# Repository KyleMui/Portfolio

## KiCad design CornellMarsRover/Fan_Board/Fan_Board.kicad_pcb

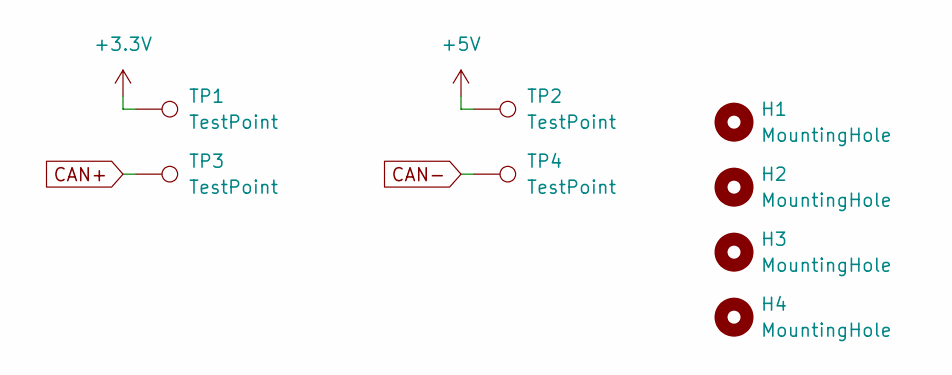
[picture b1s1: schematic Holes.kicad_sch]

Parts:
H1, H2, H3, H4: MountingHole; MountingHole_3.2mm_M3
TP1, TP2, TP3, TP4: TestPoint; TestPoint_Pad_D1.0mm

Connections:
+3.3V: TP1.1; also elsewhere on the board
+5V: TP2.1; also elsewhere on the board
CAN+: TP3.1; also elsewhere on the board
CAN-: TP4.1; also elsewhere on the board

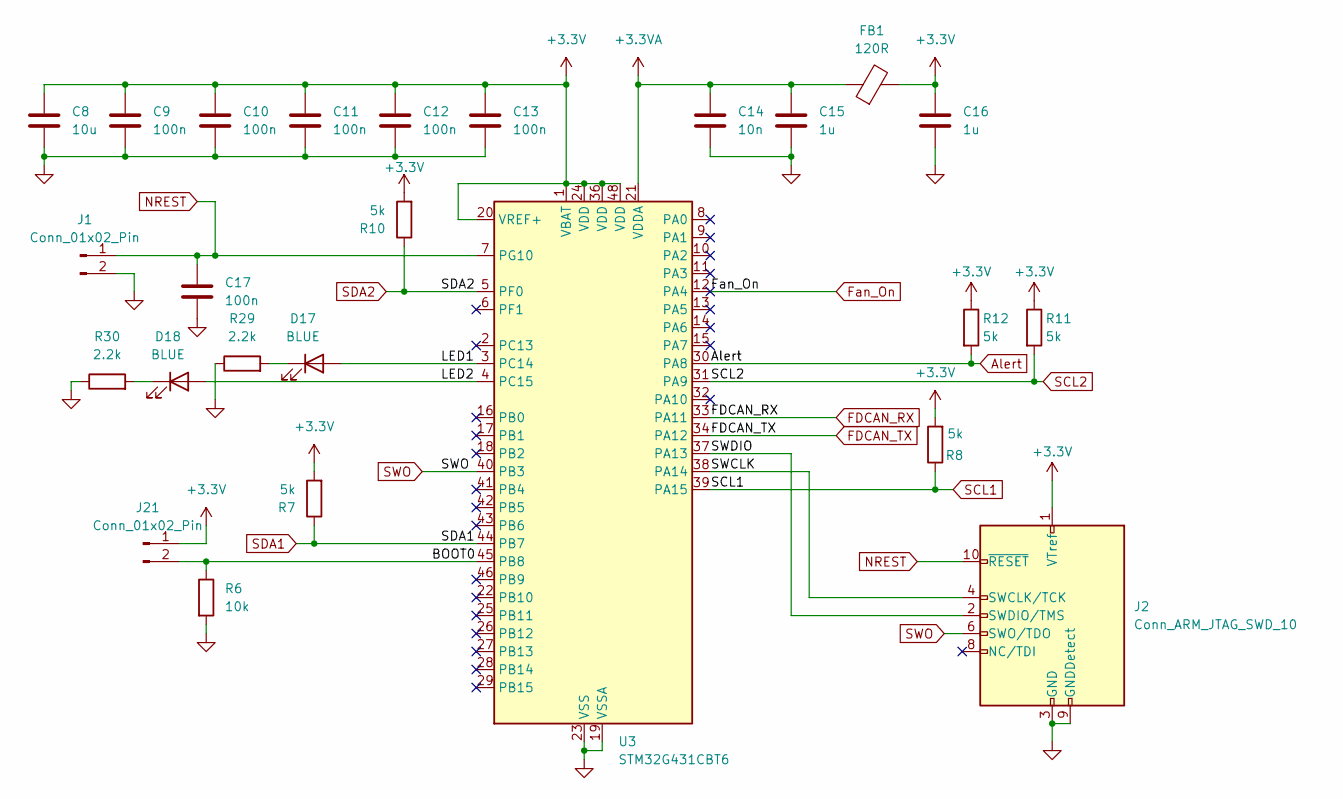
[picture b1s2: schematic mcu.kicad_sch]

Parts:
C8: 10u; C_0603_1608Metric
C9, C10, C11, C12, C13, C17: 100n; C_0402_1005Metric
C14: 10n; C_0402_1005Metric
C15, C16: 1u; C_0402_1005Metric
D17, D18: BLUE; LED_0603_1608Metric
FB1: 120R; L_0603_1608Metric
J1: Conn_01x02_Pin; PinHeader_1x02_P2.54mm_Horizontal
J2: Conn_ARM_JTAG_SWD_10; PinHeader_2x05_P1.27mm_Vertical
J21: Conn_01x02_Pin; PinHeader_1x02_P2.54mm_Vertical
R6: 10k; R_0402_1005Metric
R7, R8, R10, R11, R12: 5k; R_0402_1005Metric
R29, R30: 2.2k; R_0402_1005Metric
U3: STM32G431CBT6; LQFP-48_7x7mm_P0.5mm

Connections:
+3.3V: C8.1, C9.1, C10.1, C11.1, C12.1, C13.1, C16.1, FB1.2, J2.1 (VTref), J21.1, R7.2, R8.2, R10.2, R11.1, R12.1, U3.1 (VBAT), U3.20 (VREF+), U3.24 (VDD), U3.36 (VDD), U3.48 (VDD); also elsewhere on the board
+3.3VA: C14.1, C15.1, FB1.1, U3.21 (VDDA)
/MCU/BOOT0: J21.2, R6.1, U3.45 (PB8)
/MCU/LED1: D17.2 (A), U3.3 (PC14)
/MCU/LED2: D18.2 (A), U3.4 (PC15)
/MCU/SWCLK: J2.4 (SWCLK/TCK), U3.38 (PA14)
/MCU/SWDIO: J2.2 (SWDIO/TMS), U3.37 (PA13)
Alert: R12.2, U3.30 (PA8); also elsewhere on the board
FDCAN_RX: U3.33 (PA11); also elsewhere on the board
FDCAN_TX: U3.34 (PA12); also elsewhere on the board
Fan_On: U3.12 (PA4); also elsewhere on the board
GND: C8.2, C9.2, C10.2, C11.2, C12.2, C13.2, C14.2, C15.2, C16.2, C17.2, J1.2, J2.3 (GND), J2.5 (GND), J2.9 (GNDDetect), R6.2, R29.1, R30.1, U3.19 (VSSA), U3.23 (VSS), U3.35 (VSS), U3.47 (VSS); also elsewhere on the board
NREST: C17.1, J1.1, J2.10 (~RESET), U3.7 (PG10)
unnamed: D17.1 (K), R29.2
unnamed: D18.1 (K), R30.2
SCL1: R8.1, U3.39 (PA15); also elsewhere on the board
SCL2: R11.2, U3.31 (PA9); also elsewhere on the board
SDA1: R7.1, U3.44 (PB7); also elsewhere on the board
SDA2: R10.1, U3.5 (PF0); also elsewhere on the board
SWO: J2.6 (SWO/TDO), U3.40 (PB3)

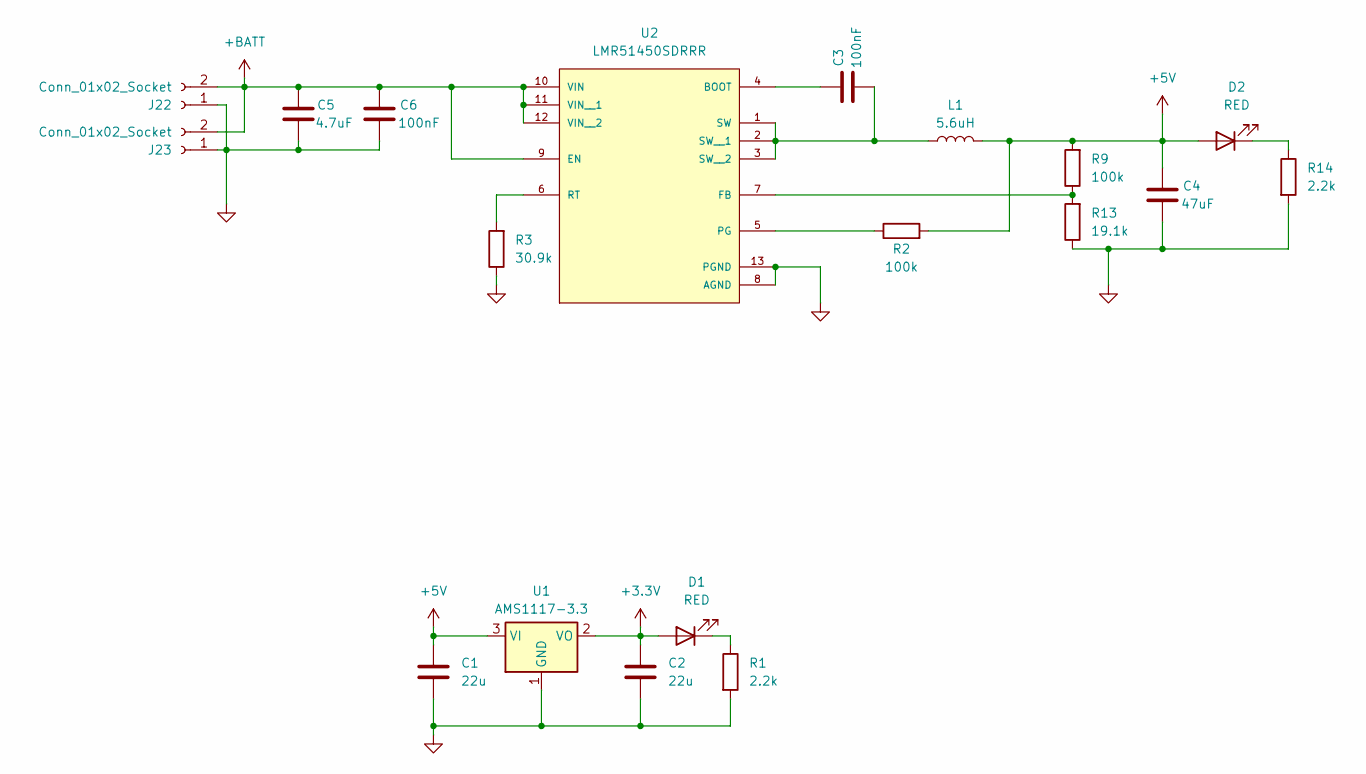
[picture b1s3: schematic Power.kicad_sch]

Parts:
C1, C2: 22u; C_0805_2012Metric
C3, C6: 100nF; C_0402_1005Metric
C4: 47uF; C_1210_3225Metric
C5: 4.7uF; C_1206_3216Metric
D1, D2: RED; LED_0603_1608Metric
J22, J23: Conn_01x02_Socket; AMASS_XT30PW-M_1x02_P2.50mm_Horizontal
L1: 5.6uH; L_Vishay_IHLP-4040
R1, R14: 2.2k; R_0402_1005Metric
R2, R9: 100k; R_0603_1608Metric
R3: 30.9k; R_0603_1608Metric
R13: 19.1k; R_0603_1608Metric
U1: AMS1117-3.3; SOT-223-3_TabPin2
U2: LMR51450SDRRR; CONV_LMR51450SDRRR; PARTREV December 2022

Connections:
+3.3V: C2.1, D1.2 (A), U1.2 (VO); also elsewhere on the board
+5V: C1.1, C4.1, D2.2 (A), L1.2, R2.2, R9.2, U1.3 (VI); also elsewhere on the board
+BATT: C5.1, C6.1, J22.2, J23.2, U2.9 (EN), U2.10 (VIN), U2.11 (VIN__1), U2.12 (VIN__2)
GND: C1.2, C2.2, C4.2, C5.2, C6.2, J22.1, J23.1, R1.2, R3.1, R13.1, R14.2, U1.1 (GND), U2.8 (AGND), U2.13 (PGND); also elsewhere on the board
unnamed: D1.1 (K), R1.1
unnamed: D2.1 (K), R14.1
unnamed: C3.1, U2.4 (BOOT)
unnamed: R9.1, R13.2, U2.7 (FB)
unnamed: R2.1, U2.5 (PG)
unnamed: R3.2, U2.6 (RT)
unnamed: C3.2, L1.1, U2.1 (SW), U2.2 (SW__1), U2.3 (SW__2)

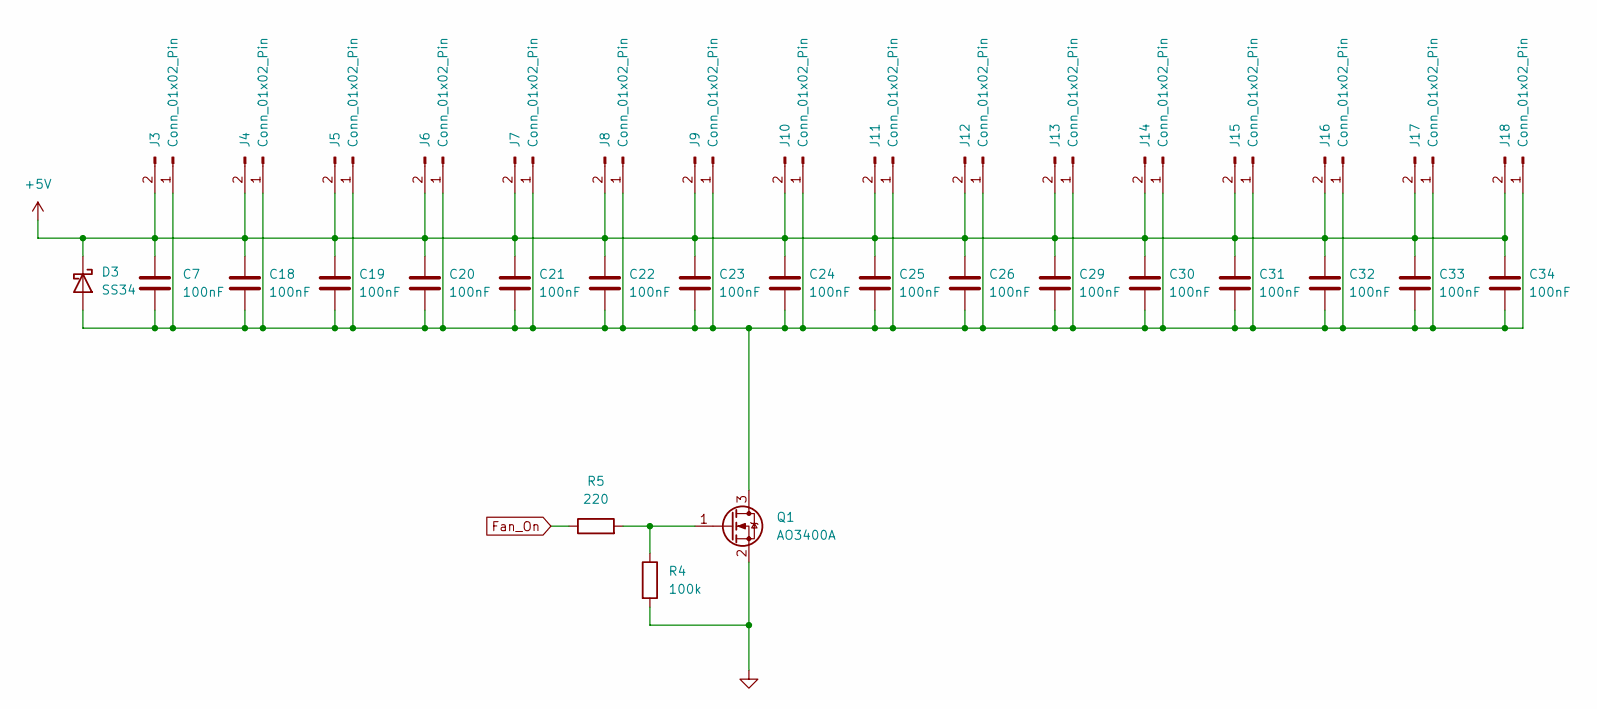
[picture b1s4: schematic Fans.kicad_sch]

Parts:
C7, C18, C19, C20, C21, C22, C23, C24, C25, C26, C29, C30, C31, C32, C33, C34: 100nF; C_0402_1005Metric
D3: SS34; D_SMA
J3, J4, J5, J6, J7, J8, J9, J10, J11, J12, J13, J14, J15, J16, J17, J18: Conn_01x02_Pin; JST_S2B-PH-SM4-TB
Q1: AO3400A; SOT-23
R4: 100k; R_0603_1608Metric
R5: 220; R_0603_1608Metric

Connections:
+5V: C7.1, C18.1, C19.1, C20.1, C21.1, C22.1, C23.1, C24.1, C25.1, C26.1, C29.1, C30.1, C31.1, C32.1, C33.1, C34.1, D3.1 (K), J3.2, J4.2, J5.2, J6.2, J7.2, J8.2, J9.2, J10.2, J11.2, J12.2, J13.2, J14.2, J15.2, J16.2, J17.2, J18.2; also elsewhere on the board
Fan_On: R5.1; also elsewhere on the board
GND: Q1.2 (S), R4.2; also elsewhere on the board
unnamed: C7.2, C18.2, C19.2, C20.2, C21.2, C22.2, C23.2, C24.2, C25.2, C26.2, C29.2, C30.2, C31.2, C32.2, C33.2, C34.2, D3.2 (A), J3.1, J4.1, J5.1, J6.1, J7.1, J8.1, J9.1, J10.1, J11.1, J12.1, J13.1, J14.1, J15.1, J16.1, J17.1, J18.1, Q1.3 (D)
unnamed: Q1.1 (G), R4.1, R5.2

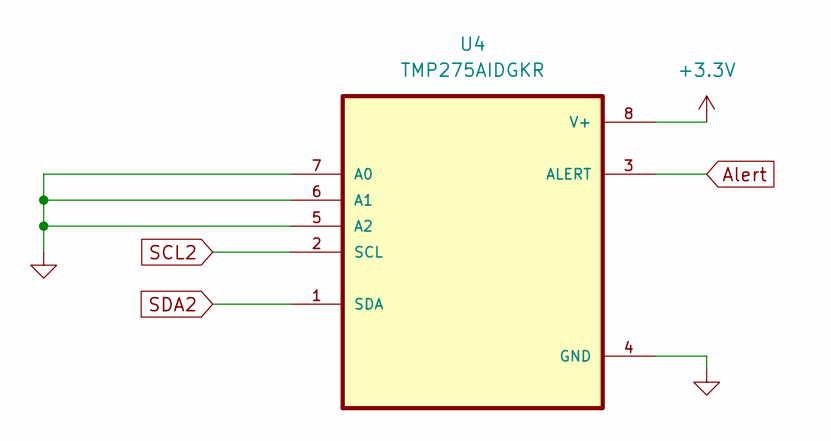
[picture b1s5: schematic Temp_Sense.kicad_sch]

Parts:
U4: TMP275AIDGKR; SOP65P490X110-8N

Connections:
+3.3V: U4.8 (V+); also elsewhere on the board
Alert: U4.3 (ALERT); also elsewhere on the board
GND: U4.4 (GND), U4.5 (A2), U4.6 (A1), U4.7 (A0); also elsewhere on the board
SCL2: U4.2 (SCL); also elsewhere on the board
SDA2: U4.1 (SDA); also elsewhere on the board

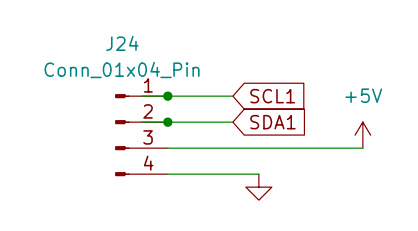
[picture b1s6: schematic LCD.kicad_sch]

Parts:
J24: Conn_01x04_Pin; PinHeader_1x04_P2.54mm_Horizontal

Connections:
+5V: J24.3; also elsewhere on the board
GND: J24.4; also elsewhere on the board
SCL1: J24.1; also elsewhere on the board
SDA1: J24.2; also elsewhere on the board

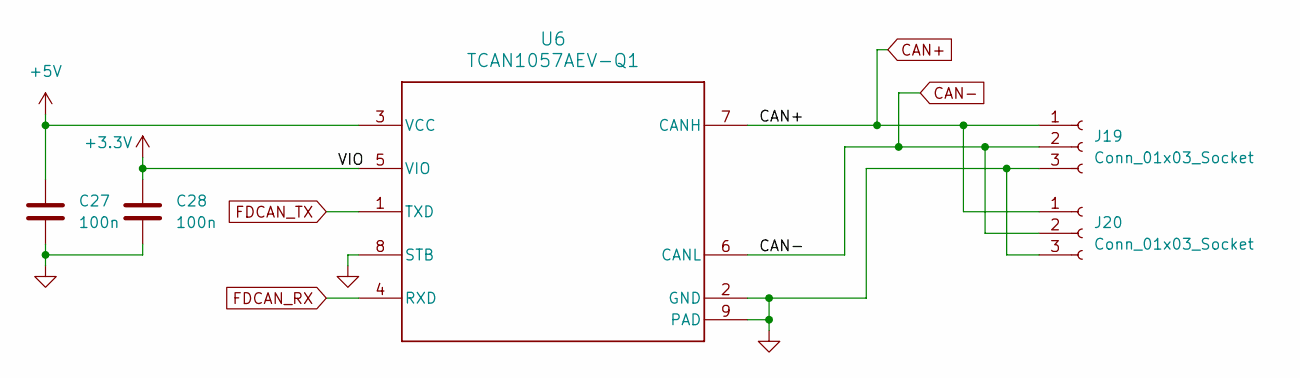
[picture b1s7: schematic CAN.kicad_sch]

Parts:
C27, C28: 100n; C_0402_1005Metric
J19, J20: Conn_01x03_Socket; JST_PH_S3B-PH-SM4-TB_1x03-1MP_P2.00mm_Horizontal
U6: TCAN1057AEV-Q1; SOIC-8_3.9x4.9mm_P1.27mm; MPN TCAN1057AEVDRQ1

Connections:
+3.3V: C28.1, U6.5 (VIO); also elsewhere on the board
+5V: C27.1, U6.3 (VCC); also elsewhere on the board
CAN+: J19.1, J20.1, U6.7 (CANH); also elsewhere on the board
CAN-: J19.2, J20.2, U6.6 (CANL); also elsewhere on the board
FDCAN_RX: U6.4 (RXD); also elsewhere on the board
FDCAN_TX: U6.1 (TXD); also elsewhere on the board
GND: C27.2, C28.2, J19.3, J20.3, U6.2 (GND), U6.8 (STB), U6.9 (PAD); also elsewhere on the board

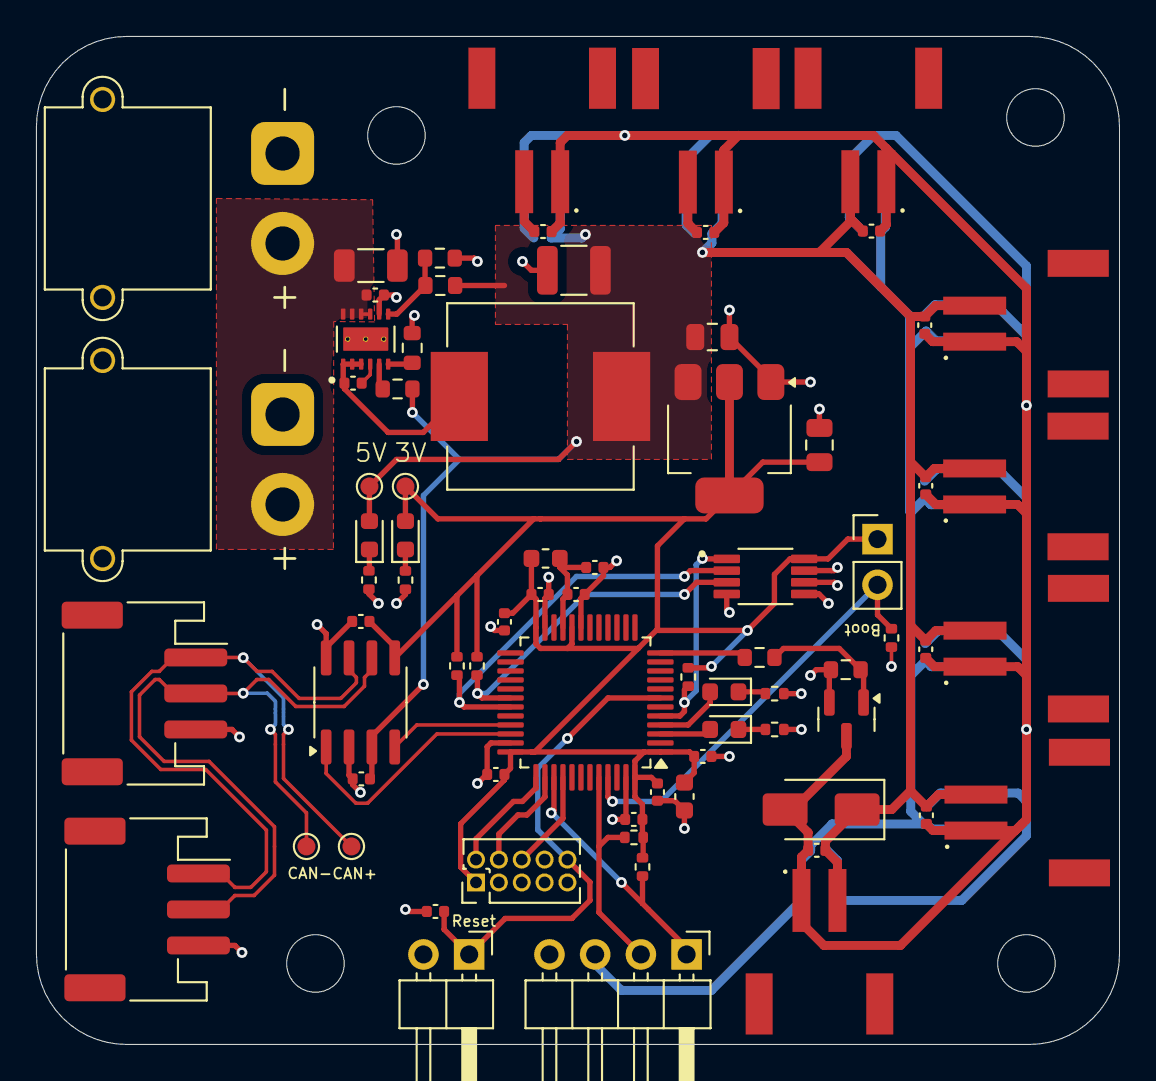
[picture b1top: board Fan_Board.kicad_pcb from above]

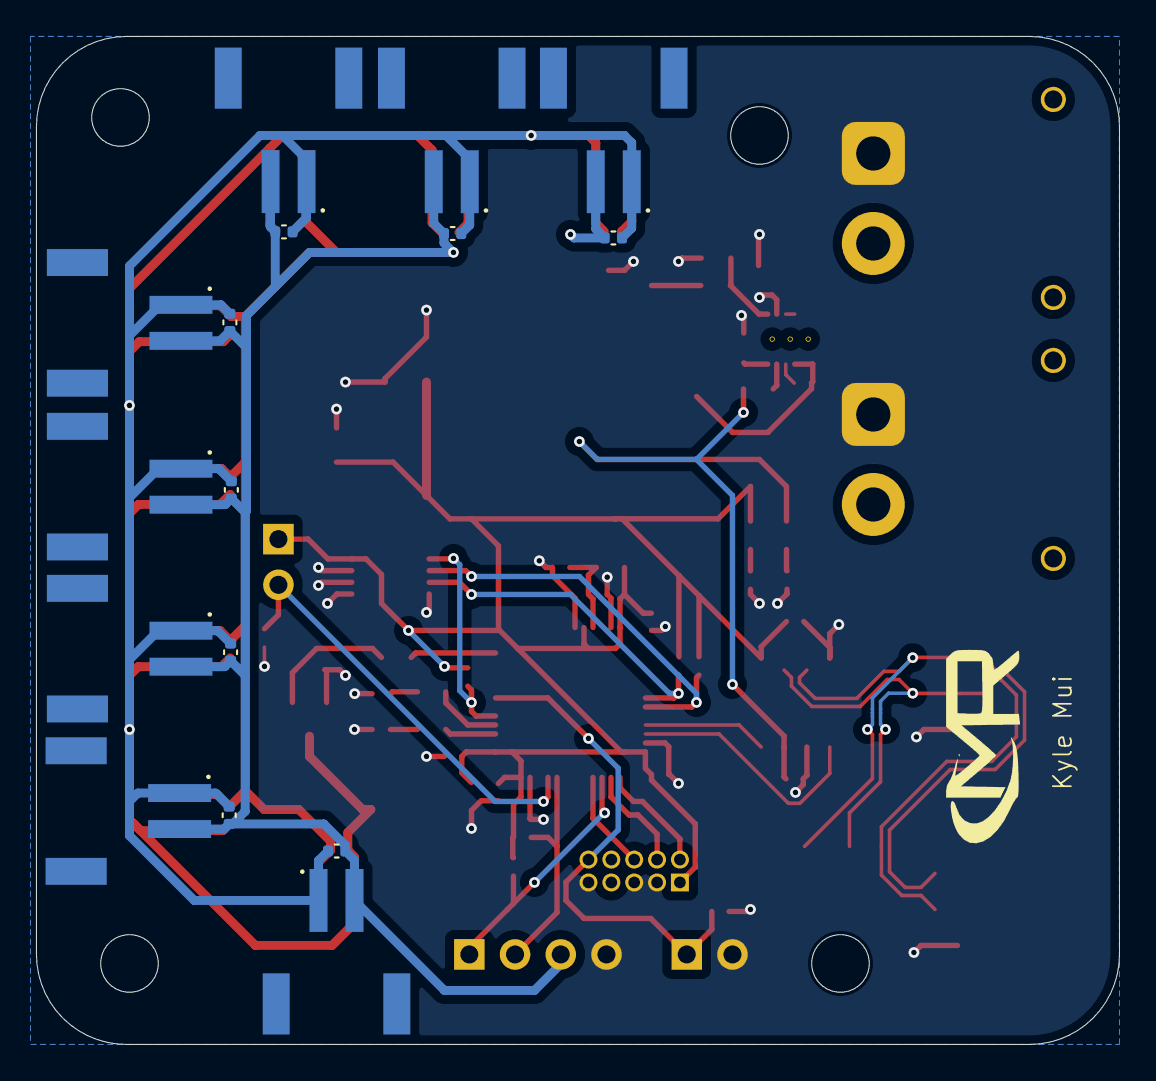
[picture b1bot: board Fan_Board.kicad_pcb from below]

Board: 2 copper layers, 60.2 x 56.0 mm, 95 parts (16 on the bottom side), 33 nets.

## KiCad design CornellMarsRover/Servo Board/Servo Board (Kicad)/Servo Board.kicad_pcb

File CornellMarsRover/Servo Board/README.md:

# 16-Channel Servo Controller Board

## Overview
This custom board is a servo controller that can run up to 16 independent servo motors. Each motor is controlled by accurate hardware PWM signals generated by the STM32. The system runs off a 28-volt power input, which is regulated on the board to provide power for both the logic circuits and the shared servo power rail.

---

## Key Features
- Controls 16 independent servo motors
- Uses a STM32G431CBT6 microcontroller
- CAN FD communication interface for high-speed, reliable data exchange between subsystems
- 28 V power input with onboard voltage regulation
- Common power rail for all servo outputs
- SWD header for programming and debugging

---

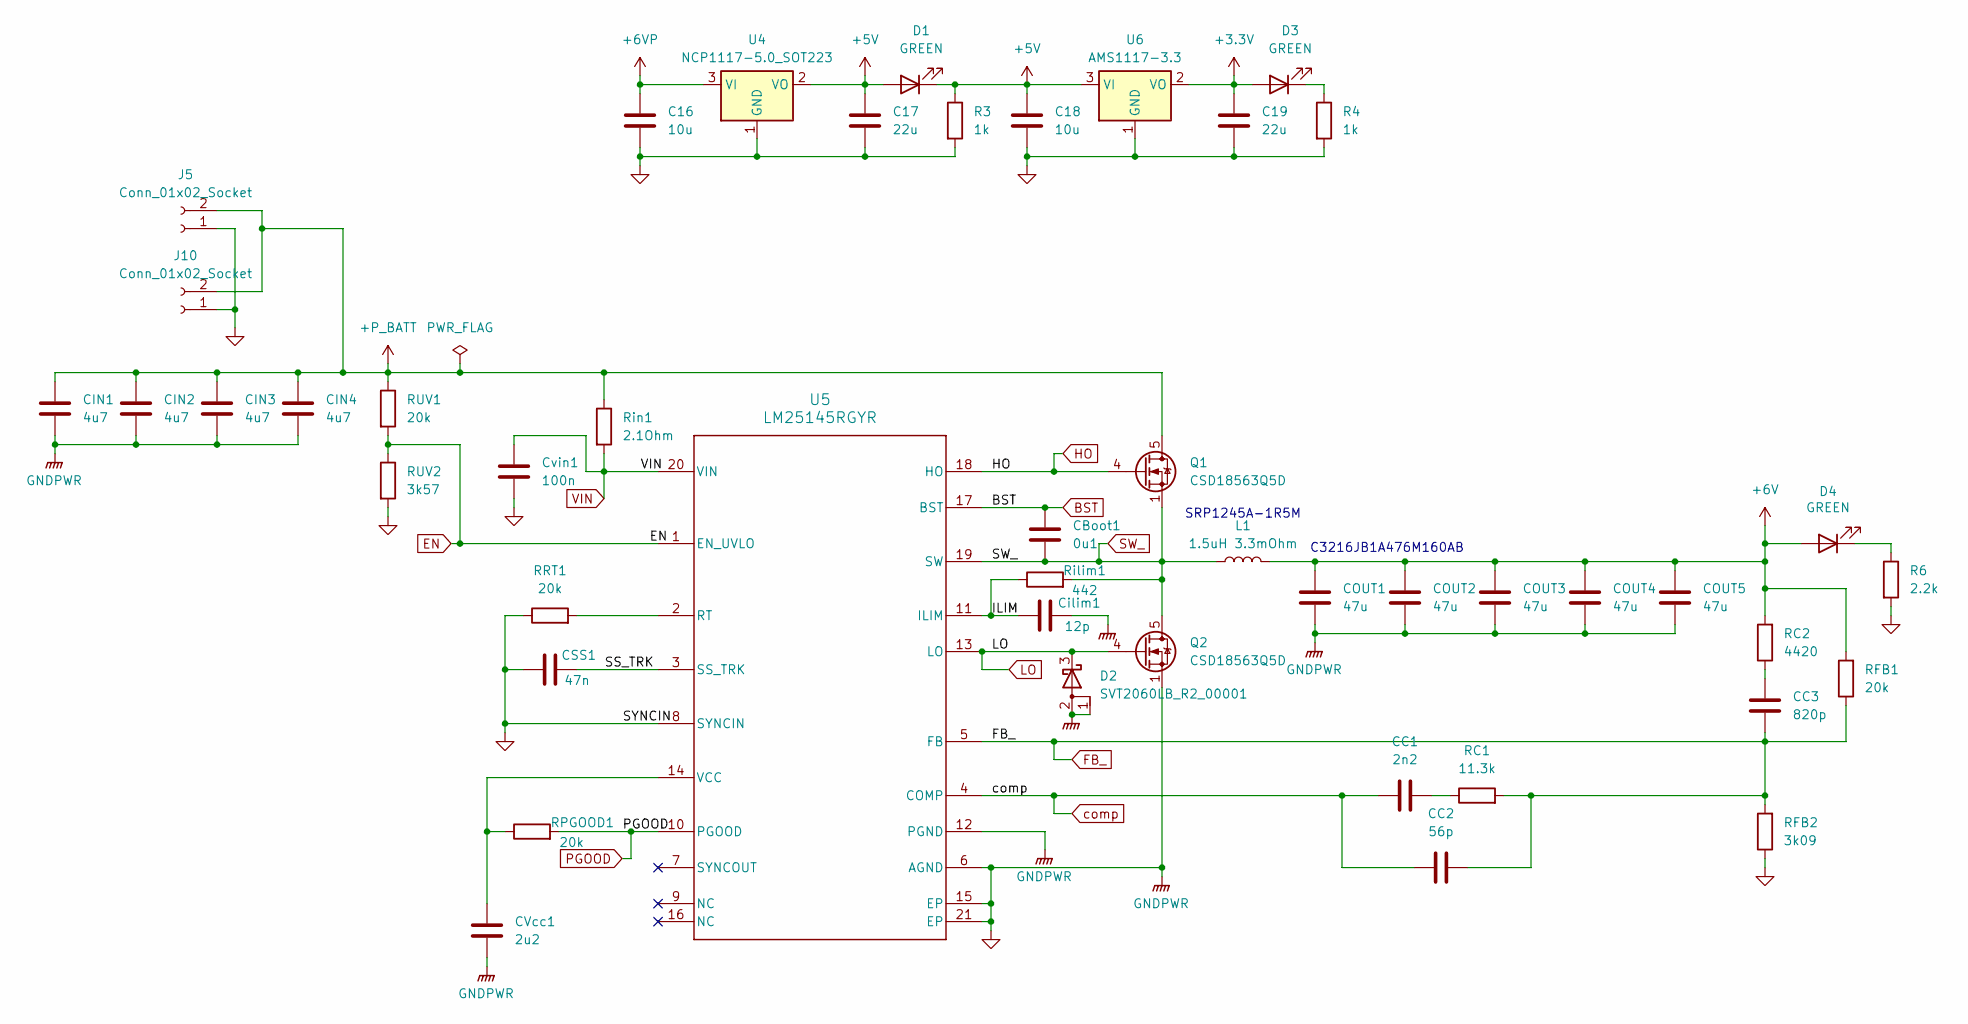
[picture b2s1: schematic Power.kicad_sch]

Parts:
C16, C18: 10u; C_0805_2012Metric
C17, C19: 22u; C_0805_2012Metric
CBoot1: 0u1; C_0603_1608Metric
CC1: 2n2; C_0402_1005Metric
CC2: 56p; C_0402_1005Metric
CC3: 820p; C_0402_1005Metric
CIN1, CIN2, CIN3, CIN4: 4u7; C_1206_3216Metric
COUT1, COUT2, COUT3, COUT4, COUT5: 47u; C_1206_3216Metric
CSS1: 47n; C_0603_1608Metric
CVcc1: 2u2; C_0603_1608Metric
Cilim1: 12p; C_0402_1005Metric
Cvin1: 100n; C_0402_1005Metric
D1, D3, D4: GREEN; LED_0603_1608Metric
D2: SVT2060LB_R2_00001; TO-277B
J5, J10: Conn_01x02_Socket; AMASS_XT30PW-M_1x02_P2.50mm_Horizontal
L1: 1.5uH 3.3mOhm; IND_AMDLA1306Q-101M
Q1, Q2: CSD18563Q5D; TDSON-8-1
R3, R4: 1k; R_0402_1005Metric
R6: 2.2k; R_0402_1005Metric
RC1: 11.3k; R_0402_1005Metric
RC2: 4420; R_0402_1005Metric
RFB1: 20k; R_0402_1005Metric
RFB2: 3k09; R_0402_1005Metric
RPGOOD1: 20k; R_0402_1005Metric
RRT1: 20k; R_0402_1005Metric
RUV1: 20k; R_0603_1608Metric
RUV2: 3k57; R_0402_1005Metric
Rilim1: 442; R_0805_2012Metric
Rin1: 2.1Ohm; R_0402_1005Metric
U4: NCP1117-5.0_SOT223; SOT-223-3_TabPin2
U5: LM25145RGYR; RGY0020B
U6: AMS1117-3.3; SOT-223-3_TabPin2

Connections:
+3.3V: C19.1, D3.2 (A), U6.2 (VO); also elsewhere on the board
+5V: C17.1, C18.1, D1.1 (K), D1.2 (A), R3.1, U4.2 (VO), U6.3 (VI); also elsewhere on the board
+6V: COUT1.1, COUT2.1, COUT3.1, COUT4.1, COUT5.1, D4.2 (A), L1.2, RC2.2, RFB1.2; also elsewhere on the board
+6VP: C16.1, U4.3 (VI); also elsewhere on the board
+P_BATT: CIN1.1, CIN2.1, CIN3.1, CIN4.1, J5.2, J10.2, Q1.5 (D), RUV1.1, Rin1.1; also elsewhere on the board
/Power/ILIM: Cilim1.1, Rilim1.1, U5.11 (ILIM)
/Power/SS_TRK: CSS1.2, U5.3 (SS_TRK)
BST: CBoot1.1, U5.17 (BST); also elsewhere on the board
EN: RUV1.2, RUV2.1, U5.1 (EN_UVLO); also elsewhere on the board
FB_: CC2.2, CC3.1, RC1.2, RFB1.1, RFB2.2, U5.5 (FB); also elsewhere on the board
GND: C16.2, C17.2, C18.2, C19.2, CIN1.2, CIN2.2, CIN3.2, CIN4.2, COUT1.2, COUT2.2, COUT3.2, COUT4.2, COUT5.2, CSS1.1, CVcc1.2, Cilim1.2, Cvin1.2, D2.1 (A), D2.2 (A), J5.1, J10.1, Q2.1 (S), Q2.2 (S), Q2.3 (S), R3.2, R4.2, R6.2, RFB2.1, RRT1.1, RUV2.2, U4.1 (GND), U5.6 (AGND), U5.8 (SYNCIN), U5.12 (PGND), U5.15 (EP), U5.21 (EP), U6.1 (GND); also elsewhere on the board
HO: Q1.4 (G), U5.18 (HO); also elsewhere on the board
LO: D2.3 (K), Q2.4 (G), U5.13 (LO); also elsewhere on the board
unnamed: CC1.2, RC1.1
unnamed: CC3.2, RC2.1
unnamed: D3.1 (K), R4.1
unnamed: D4.1 (K), R6.1
unnamed: RRT1.2, U5.2 (RT)
unnamed: CVcc1.1, RPGOOD1.1, U5.14 (VCC)
PGOOD: RPGOOD1.2, U5.10 (PGOOD); also elsewhere on the board
SW_: CBoot1.2, L1.1, Q1.1 (S), Q1.2 (S), Q1.3 (S), Q2.5 (D), Rilim1.2, U5.19 (SW); also elsewhere on the board
VIN: Cvin1.1, Rin1.2, U5.20 (VIN); also elsewhere on the board
comp: CC1.1, CC2.1, U5.4 (COMP); also elsewhere on the board

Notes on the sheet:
SRP1245A-1R5M
C3216JB1A476M160AB

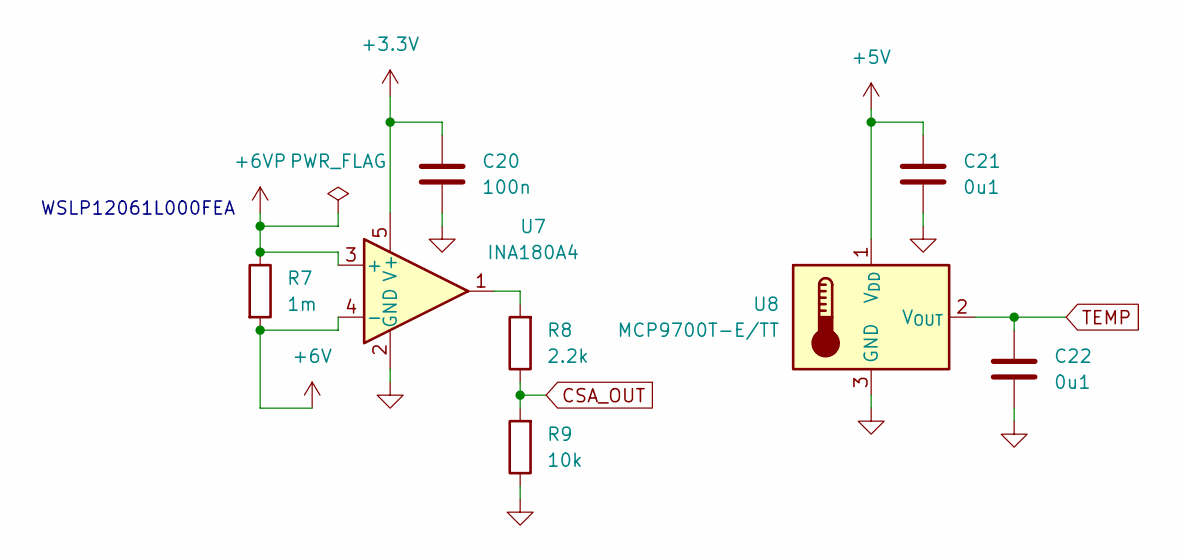
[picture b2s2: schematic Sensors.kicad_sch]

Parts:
C20: 100n; C_0402_1005Metric
C21, C22: 0u1; C_0402_1005Metric
R7: 1m; R_1206_3216Metric
R8: 2.2k; R_0402_1005Metric
R9: 10k; R_0402_1005Metric
U7: INA180A4; SOT-23-5
U8: MCP9700T-E/TT; SOT-23-3

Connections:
+3.3V: C20.1, U7.5 (V+); also elsewhere on the board
+5V: C21.1, U8.1 (V_{DD}); also elsewhere on the board
+6V: R7.2, U7.4 (-); also elsewhere on the board
+6VP: R7.1, U7.3 (+); also elsewhere on the board
CSA_OUT: R8.1, R9.2; also elsewhere on the board
GND: C20.2, C21.2, C22.2, R9.1, U7.2 (GND), U8.3 (GND); also elsewhere on the board
unnamed: R8.2, U7.1
TEMP: C22.1, U8.2 (V_{OUT}); also elsewhere on the board

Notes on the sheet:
WSLP12061L000FEA

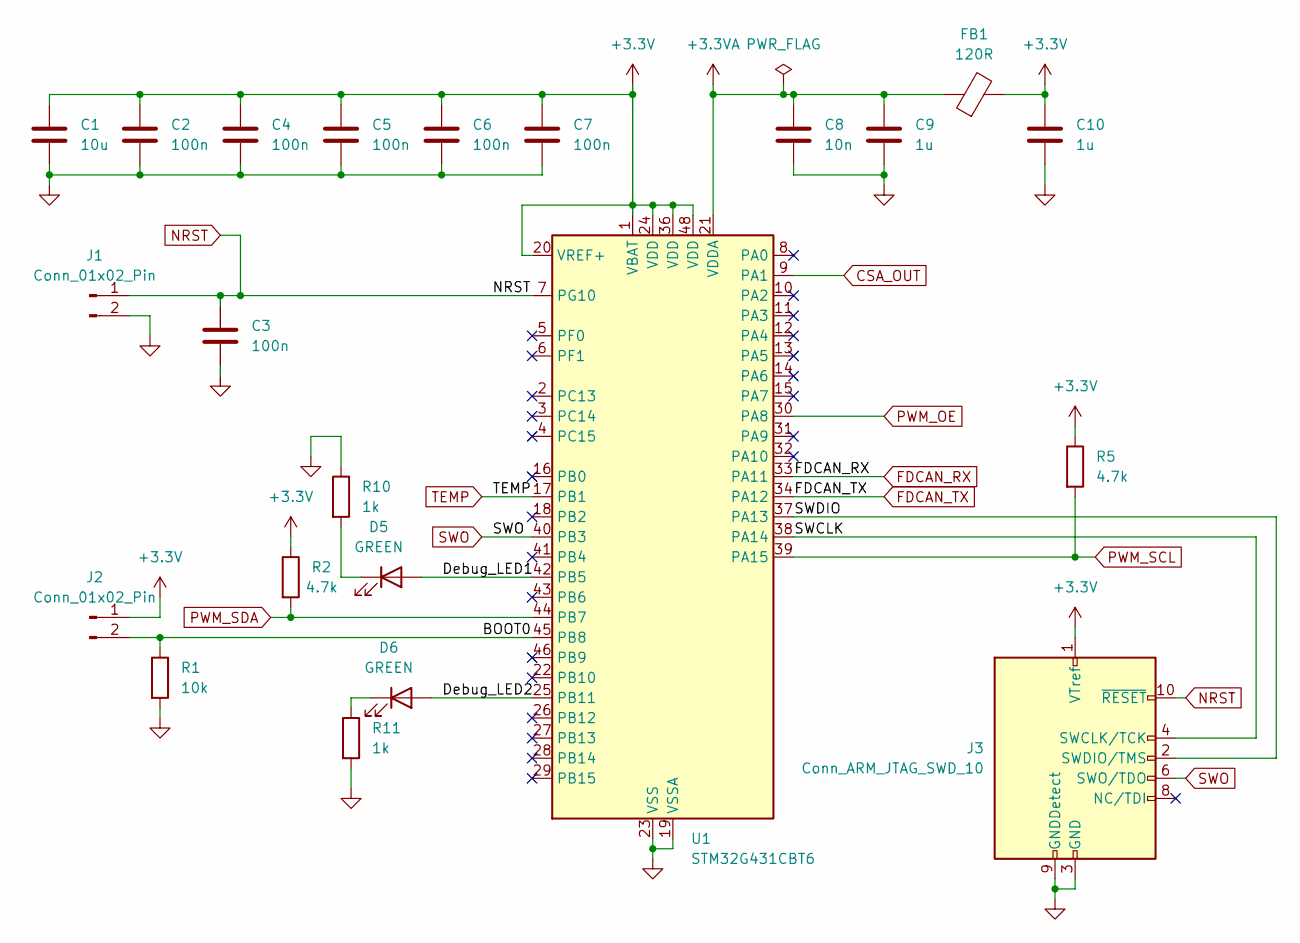
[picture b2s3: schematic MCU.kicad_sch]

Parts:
C1: 10u; C_0603_1608Metric
C2, C3, C4, C5, C6, C7: 100n; C_0402_1005Metric
C8: 10n; C_0402_1005Metric
C9, C10: 1u; C_0402_1005Metric
D5, D6: GREEN; LED_0603_1608Metric
FB1: 120R; L_0603_1608Metric
J1: Conn_01x02_Pin; PinHeader_1x02_P2.54mm_Horizontal
J2: Conn_01x02_Pin; PinHeader_1x02_P2.54mm_Vertical
J3: Conn_ARM_JTAG_SWD_10; PinHeader_2x05_P1.27mm_Vertical
R1: 10k; R_0402_1005Metric
R2, R5: 4.7k; R_0402_1005Metric
R10, R11: 1k; R_0402_1005Metric
U1: STM32G431CBT6; LQFP-48_7x7mm_P0.5mm

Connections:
+3.3V: C1.1, C2.1, C4.1, C5.1, C6.1, C7.1, C10.1, FB1.2, J2.1, J3.1 (VTref), R2.1, R5.1, U1.1 (VBAT), U1.20 (VREF+), U1.24 (VDD), U1.36 (VDD), U1.48 (VDD); also elsewhere on the board
+3.3VA: C8.1, C9.1, FB1.1, U1.21 (VDDA)
/MCU/BOOT0: J2.2, R1.1, U1.45 (PB8)
/MCU/Debug_LED1: D5.2 (A), U1.42 (PB5)
/MCU/Debug_LED2: D6.2 (A), U1.25 (PB11)
/MCU/SWCLK: J3.4 (SWCLK/TCK), U1.38 (PA14)
/MCU/SWDIO: J3.2 (SWDIO/TMS), U1.37 (PA13)
CSA_OUT: U1.9 (PA1); also elsewhere on the board
FDCAN_RX: U1.33 (PA11); also elsewhere on the board
FDCAN_TX: U1.34 (PA12); also elsewhere on the board
GND: C1.2, C2.2, C3.2, C4.2, C5.2, C6.2, C7.2, C8.2, C9.2, C10.2, J1.2, J3.3 (GND), J3.5 (GND), J3.9 (GNDDetect), R1.2, R10.1, R11.2, U1.19 (VSSA), U1.23 (VSS), U1.35 (VSS), U1.47 (VSS); also elsewhere on the board
NRST: C3.1, J1.1, J3.10 (~RESET), U1.7 (PG10); also elsewhere on the board
unnamed: D5.1 (K), R10.2
unnamed: D6.1 (K), R11.1
PWM_OE: U1.30 (PA8); also elsewhere on the board
PWM_SCL: R5.2, U1.39 (PA15); also elsewhere on the board
PWM_SDA: R2.2, U1.44 (PB7); also elsewhere on the board
SWO: J3.6 (SWO/TDO), U1.40 (PB3)
TEMP: U1.17 (PB1); also elsewhere on the board

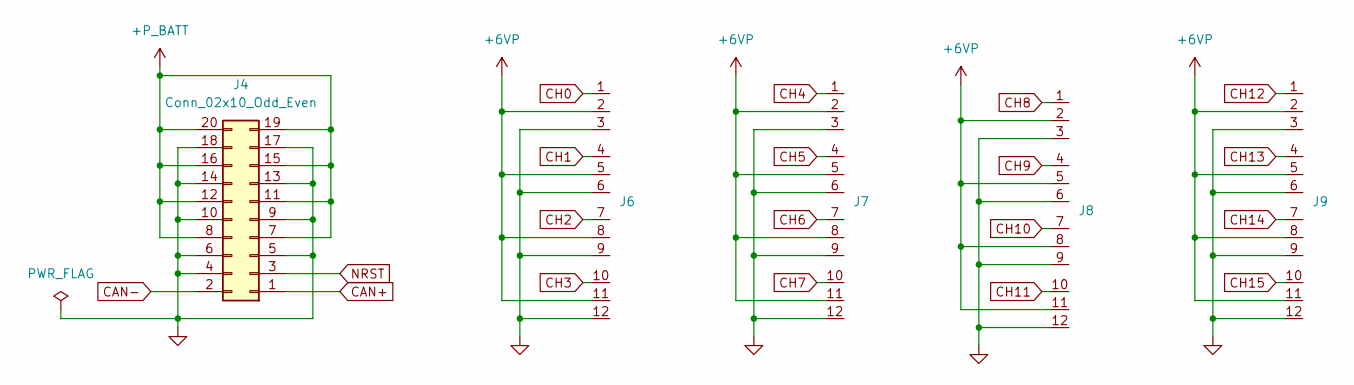
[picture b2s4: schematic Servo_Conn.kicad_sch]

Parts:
J4: Conn_02x10_Odd_Even; PinSocket_2x10_P2.54mm_Horizontal
J6, J7, J8, J9: Conn_03x4

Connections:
+6VP: J6.2, J6.5, J6.8, J6.11, J7.2, J7.5, J7.8, J7.11, J8.2, J8.5, J8.8, J8.11, J9.2, J9.5, J9.8, J9.11; also elsewhere on the board
+P_BATT: J4.7, J4.8, J4.11, J4.12, J4.15, J4.16, J4.19, J4.20; also elsewhere on the board
CAN+: J4.1; also elsewhere on the board
CAN-: J4.2; also elsewhere on the board
CH0: J6.1; also elsewhere on the board
CH1: J6.4; also elsewhere on the board
CH2: J6.7; also elsewhere on the board
CH3: J6.10; also elsewhere on the board
CH4: J7.1; also elsewhere on the board
CH5: J7.4; also elsewhere on the board
CH6: J7.7; also elsewhere on the board
CH7: J7.10; also elsewhere on the board
CH8: J8.1; also elsewhere on the board
CH9: J8.4; also elsewhere on the board
CH10: J8.7; also elsewhere on the board
CH11: J8.10; also elsewhere on the board
CH12: J9.1; also elsewhere on the board
CH13: J9.4; also elsewhere on the board
CH14: J9.7; also elsewhere on the board
CH15: J9.10; also elsewhere on the board
GND: J4.4, J4.5, J4.6, J4.9, J4.10, J4.13, J4.14, J4.17, J4.18, J6.3, J6.6, J6.9, J6.12, J7.3, J7.6, J7.9, J7.12, J8.3, J8.6, J8.9, J8.12, J9.3, J9.6, J9.9, J9.12; also elsewhere on the board
NRST: J4.3; also elsewhere on the board

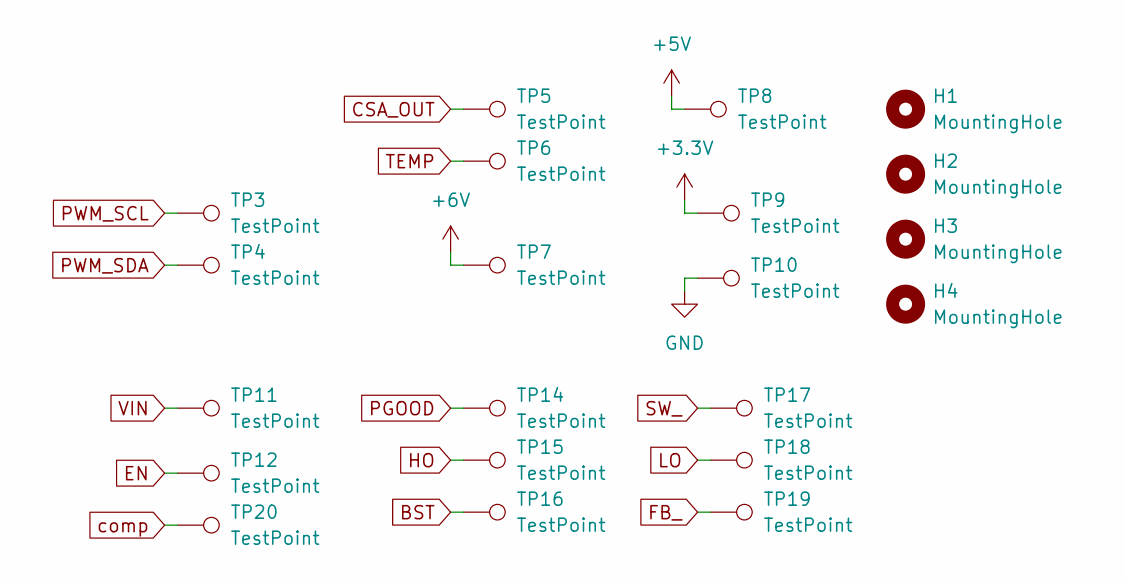
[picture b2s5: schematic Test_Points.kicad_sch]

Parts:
H1, H2, H3, H4: MountingHole; MountingHole_2.7mm_M2.5
TP3, TP4, TP5, TP6, TP7, TP8, TP9, TP10, TP11, TP12, TP14, TP15, TP16, TP17, TP18, TP19, TP20: TestPoint; TestPoint_Pad_D1.0mm

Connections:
+3.3V: TP9.1; also elsewhere on the board
+5V: TP8.1; also elsewhere on the board
+6V: TP7.1; also elsewhere on the board
BST: TP16.1; also elsewhere on the board
CSA_OUT: TP5.1; also elsewhere on the board
EN: TP12.1; also elsewhere on the board
FB_: TP19.1; also elsewhere on the board
GND: TP10.1; also elsewhere on the board
HO: TP15.1; also elsewhere on the board
LO: TP18.1; also elsewhere on the board
PGOOD: TP14.1; also elsewhere on the board
PWM_SCL: TP3.1; also elsewhere on the board
PWM_SDA: TP4.1; also elsewhere on the board
SW_: TP17.1; also elsewhere on the board
TEMP: TP6.1; also elsewhere on the board
VIN: TP11.1; also elsewhere on the board
comp: TP20.1; also elsewhere on the board

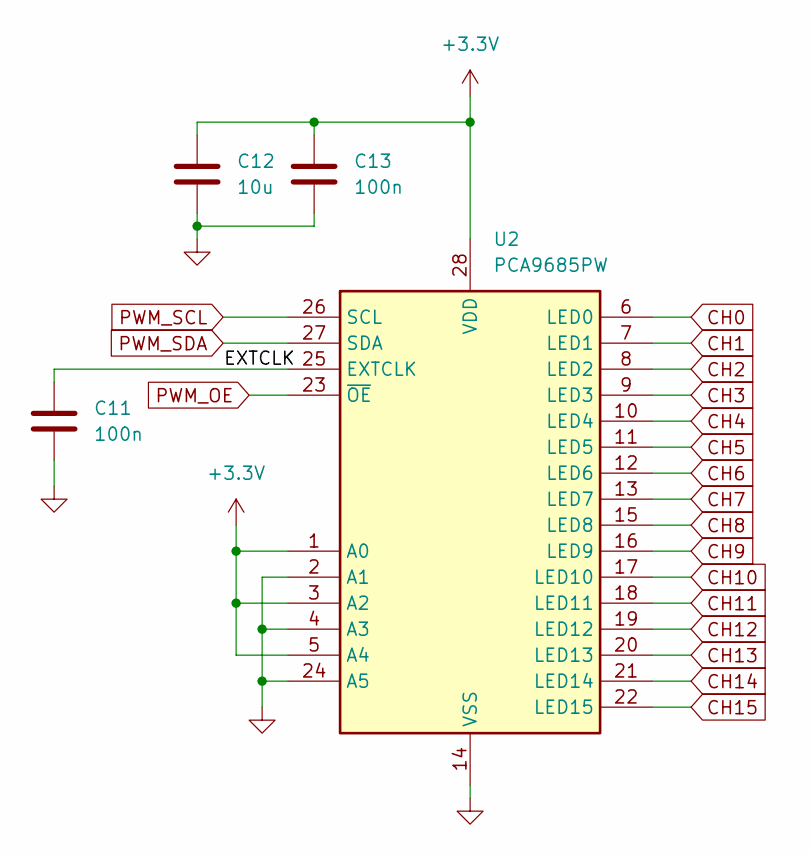
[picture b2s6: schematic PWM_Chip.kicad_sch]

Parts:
C11, C13: 100n; C_0402_1005Metric
C12: 10u; C_0603_1608Metric
U2: PCA9685PW; TSSOP-28_4.4x9.7mm_P0.65mm

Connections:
+3.3V: C12.1, C13.1, U2.1 (A0), U2.3 (A2), U2.5 (A4), U2.28 (VDD); also elsewhere on the board
/PWM Chip/EXTCLK: C11.1, U2.25 (EXTCLK)
CH0: U2.6 (LED0); also elsewhere on the board
CH1: U2.7 (LED1); also elsewhere on the board
CH2: U2.8 (LED2); also elsewhere on the board
CH3: U2.9 (LED3); also elsewhere on the board
CH4: U2.10 (LED4); also elsewhere on the board
CH5: U2.11 (LED5); also elsewhere on the board
CH6: U2.12 (LED6); also elsewhere on the board
CH7: U2.13 (LED7); also elsewhere on the board
CH8: U2.15 (LED8); also elsewhere on the board
CH9: U2.16 (LED9); also elsewhere on the board
CH10: U2.17 (LED10); also elsewhere on the board
CH11: U2.18 (LED11); also elsewhere on the board
CH12: U2.19 (LED12); also elsewhere on the board
CH13: U2.20 (LED13); also elsewhere on the board
CH14: U2.21 (LED14); also elsewhere on the board
CH15: U2.22 (LED15); also elsewhere on the board
GND: C11.2, C12.2, C13.2, U2.2 (A1), U2.4 (A3), U2.14 (VSS), U2.24 (A5); also elsewhere on the board
PWM_OE: U2.23 (~OE); also elsewhere on the board
PWM_SCL: U2.26 (SCL); also elsewhere on the board
PWM_SDA: U2.27 (SDA); also elsewhere on the board

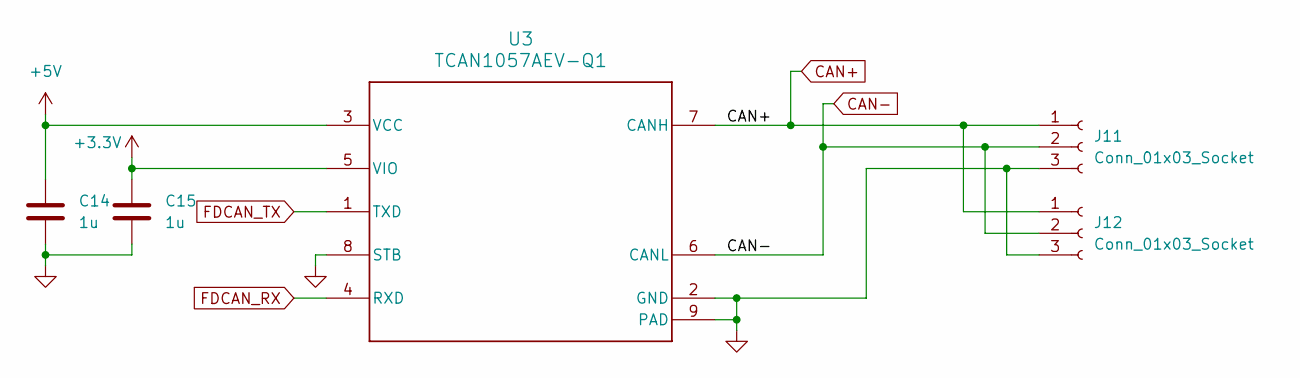
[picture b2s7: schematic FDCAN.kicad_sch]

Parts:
C14, C15: 1u; C_0402_1005Metric
J11, J12: Conn_01x03_Socket; JST_PH_S3B-PH-SM4-TB_1x03-1MP_P2.00mm_Horizontal
U3: TCAN1057AEV-Q1; SOIC-8_3.9x4.9mm_P1.27mm; MPN TCAN1057AEVDRQ1

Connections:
+3.3V: C15.1, U3.5 (VIO); also elsewhere on the board
+5V: C14.1, U3.3 (VCC); also elsewhere on the board
CAN+: J11.1, J12.1, U3.7 (CANH); also elsewhere on the board
CAN-: J11.2, J12.2, U3.6 (CANL); also elsewhere on the board
FDCAN_RX: U3.4 (RXD); also elsewhere on the board
FDCAN_TX: U3.1 (TXD); also elsewhere on the board
GND: C14.2, C15.2, J11.3, J12.3, U3.2 (GND), U3.8 (STB), U3.9 (PAD); also elsewhere on the board
